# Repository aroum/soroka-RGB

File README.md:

# soroka RGB - DIY-Friendly 40% keyboard

This is a fork of the [Soroka](https://github.com/kapee1/soroka/) project with added support for the RP2040-Zero-matrix. The only modifications are to the spacer (v2), which includes a cutout to improve the viewing angle, and the addition of two optional pads on the board (v2). However, you can also use the original files with minor adjustments—see the Build Guide for more details.

### Build guide [[EN]](https://github.com/kapee1/soroka/blob/main/build%20guides/Soroka%20v2%20Build%20guide%20%5BEN%5D.md) | [[RU]](https://github.com/kapee1/soroka/blob/main/build%20guides/Soroka%20v2%20Build%20guide%20%5BRU%5D.md)

__Parts for v1 and v2 are not compatible!__

### Main features:

* Easy to build. Great for soldering practice.
* Supports all cyrillic symbols in base layer.
* Compatible with most base-kit keycap sets. No 40s addons needed.
* Optional Panasonic EVQWGD001 or EC-11 encoder
* Plate also optional. You can build keyboard without a plate to reduce cost.
* Variable bottom-row with a 3u spacebars support.
* Customizable magnet panels
* RGB matrix display 5x5
* [ZMK Studio](https://github.com/aroum/zmk-soroka)

### RGB

### Layout:

### Sizes:

## BOM:
| Part     | Quantity |
|----------|----------|
| Soroka PCB                    | 1   | 
| Soroka Plate (Optional)       | 1   | 
| Soroka Case                   | 1   | 
| Soroka Panel  (clear)         | 1   | 
| Soroka Spacer (mod)           | 1   | 
| RP2040-Zero-matrix (unsoldered pins) | 1   | 
| 1N4148w SOD-123 Diodes        | 50  | 
| Panasonic EVQWGD001 (optional)| 1   |  
| Oval feets 22x4x1.5mm         | 4   |  
| Silicone washers 2x5x1        | 9   |
| M2 x 4mm Screws               | 13  |  
| M2 Inserts 3mm (OD3.2)        | 13  |  
| Round magnets 3x1 mm          | 8   |

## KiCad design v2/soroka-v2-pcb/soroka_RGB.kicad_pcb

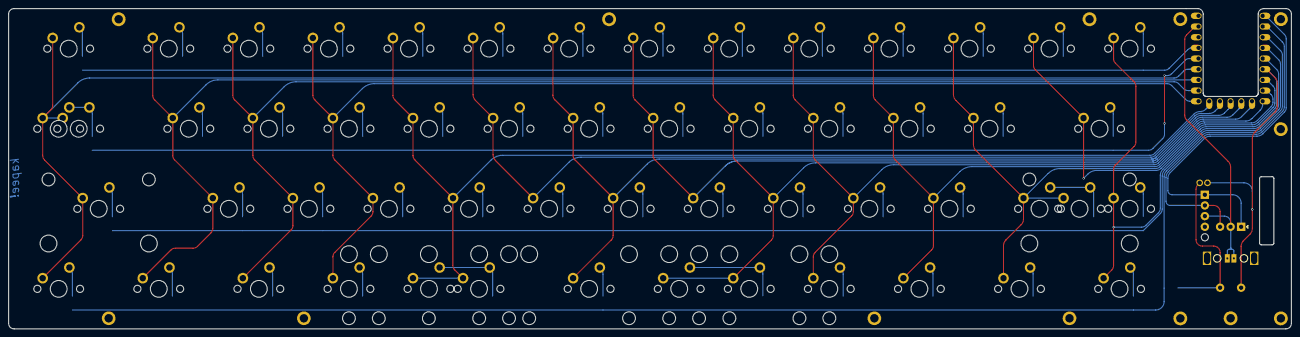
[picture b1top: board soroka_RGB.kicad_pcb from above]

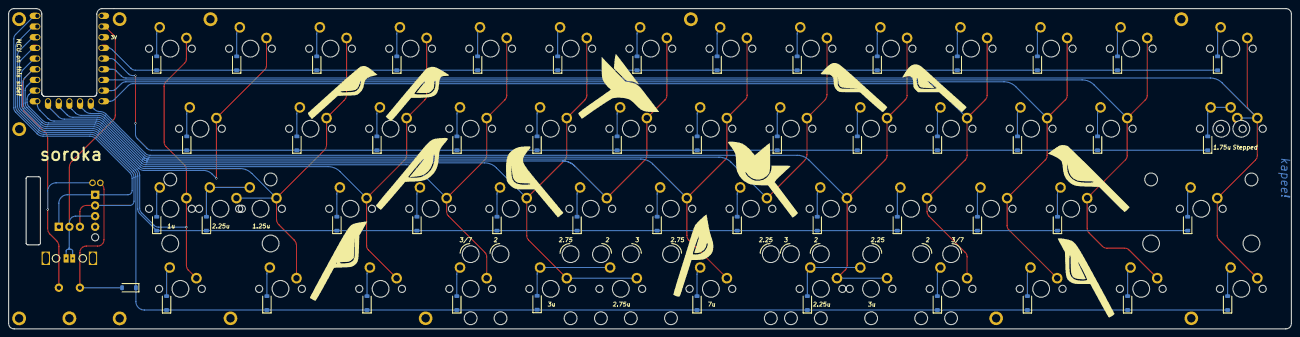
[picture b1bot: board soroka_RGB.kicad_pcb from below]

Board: 2 copper layers, 305.2 x 76.2 mm, 115 parts (52 on the bottom side), 73 nets.

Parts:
D1, D2, D3, D4, D5, D6, D7, D8, D9, D10, D11, D12, D13, D14, D15, D16, D17, D18, D19, D20, D21, D22, D23, D24, D25, D26, D27, D28, D29, D30, D31, D32, D33, D34, D35, D36, D37, D38, D39, D40, D41, D42, D43, D44, D45, D46, D47, D48, D49, D50, D51, D52: 1N4148W; D_SOD-123
MP: (no value)
RSW1, RSW1#2: SW_PUSH; SW_3x4x2_2legs_x2
SW1: MX150
SW2, SW3#2, SW4, SW5, SW6, SW7, SW8, SW9, SW10, SW11, SW12, SW13, SW14, SW16, SW17, SW18, SW19, SW20, SW21, SW22, SW23, SW24, SW25, SW26, SW29, SW30, SW31, SW32, SW33, SW34, SW35, SW36, SW37, SW38, SW45, SW50: MX100
SW3: Rotary_Encoder_Switch; EVQWGD001
SW15: Stepped; MX125
SW27: MX175
SW28: MX225R; MX225
SW39: 1.25u; MX125
SW40: 2.25u; MX225
SW41: 1u; MX100
SW42, SW43, SW44, SW51, SW52, SW53: MX125
SW46, SW49: 3u; MX300R
SW47: 2.25u; MX225R
SW48: 7u; MX100
SW54: 2.75u; MX275R
SW55: RotaryEncoder_Switch; RotaryEncoder_Alps_EC11E-Switch_Vertical_H20mm
SW55#2: 1.75u; MX175
SW**: MX200R
SW**#2: MX200R
U1: RP2040-Zero; MCU_rp2040-zero-tht

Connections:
COL0: SW1.2 (Row), SW15.2 (Row), SW28.2 (Row), SW42.2 (Row), SW55#2.2, U1.18
COL1: SW2.2 (Row), SW16.2 (Row), SW29.2 (Row), SW43.2 (Row), U1.17
COL2: SW3#2.2 (Row), SW17.2 (Row), SW30.2 (Row), SW44.2 (Row), U1.16
COL3: SW4.2 (Row), SW18.2 (Row), SW31.2 (Row), SW45.2 (Row), U1.15
COL4: SW5.2 (Row), SW19.2 (Row), SW32.2 (Row), SW46.2 (Row), SW47.2 (Row), U1.14
COL5: SW6.2 (Row), SW20.2 (Row), SW33.2 (Row), U1.13
COL6: SW7.2 (Row), SW21.2 (Row), SW34.2 (Row), SW48.2 (Row), U1.12
COL7: SW8.2 (Row), SW22.2 (Row), SW35.2 (Row), U1.11
COL8: SW9.2 (Row), SW23.2 (Row), SW36.2 (Row), SW49.2 (Row), SW54.2 (Row), U1.10
COL9: SW10.2 (Row), SW24.2 (Row), SW37.2 (Row), SW50.2 (Row), U1.9
COL10: SW11.2 (Row), SW25.2 (Row), SW38.2 (Row), SW51.2 (Row), U1.8
COL11: SW12.2 (Row), SW26.2 (Row), SW39.2 (Row), SW40.2 (Row), SW52.2 (Row), U1.7
COL12: SW3.S2, SW13.2 (Row), SW27.2 (Row), SW55.S2, U1.6
COL13: SW14.2 (Row), SW41.2 (Row), SW53.2 (Row), U1.5
ENC_CCW: SW3.A, SW55.A, U1.1
ENC_CW: SW3.B, SW55.B, U1.2
GND: RSW1.2, RSW1#2.1, SW3.C, SW55.C, U1.22
unnamed: D1.2 (A), SW1.1 (Col)
unnamed: D2.2 (A), SW2.1 (Col)
unnamed: D3.2 (A), SW3#2.1 (Col)
unnamed: D4.2 (A), SW4.1 (Col)
unnamed: D5.2 (A), SW5.1 (Col)
unnamed: D6.2 (A), SW6.1 (Col)
unnamed: D7.2 (A), SW7.1 (Col)
unnamed: D8.2 (A), SW8.1 (Col)
unnamed: D9.2 (A), SW9.1 (Col)
unnamed: D10.2 (A), SW10.1 (Col)
unnamed: D11.2 (A), SW11.1 (Col)
unnamed: D12.2 (A), SW12.1 (Col)
unnamed: D13.2 (A), SW13.1 (Col)
unnamed: D14.2 (A), SW14.1 (Col)
unnamed: D15.2 (A), SW15.1 (Col), SW55#2.1
unnamed: D16.2 (A), SW16.1 (Col)
unnamed: D17.2 (A), SW17.1 (Col)
unnamed: D18.2 (A), SW18.1 (Col)
unnamed: D19.2 (A), SW19.1 (Col)
unnamed: D20.2 (A), SW20.1 (Col)
unnamed: D21.2 (A), SW21.1 (Col)
unnamed: D22.2 (A), SW22.1 (Col)
unnamed: D23.2 (A), SW23.1 (Col)
unnamed: D24.2 (A), SW24.1 (Col)
unnamed: D25.2 (A), SW25.1 (Col)
unnamed: D26.2 (A), SW26.1 (Col)
unnamed: D27.2 (A), SW27.1 (Col)
unnamed: D28.2 (A), SW28.1 (Col)
unnamed: D29.2 (A), SW29.1 (Col)
unnamed: D30.2 (A), SW30.1 (Col)
unnamed: D31.2 (A), SW31.1 (Col)
unnamed: D32.2 (A), SW32.1 (Col)
unnamed: D33.2 (A), SW33.1 (Col)
unnamed: D34.2 (A), SW34.1 (Col)
unnamed: D35.2 (A), SW35.1 (Col)
unnamed: D36.2 (A), SW36.1 (Col)
unnamed: D37.2 (A), SW37.1 (Col)
unnamed: D38.2 (A), SW38.1 (Col)
unnamed: D39.2 (A), SW39.1 (Col), SW40.1 (Col)
unnamed: D40.2 (A), SW3.S1, SW55.S1
unnamed: D41.2 (A), SW41.1 (Col)
unnamed: D42.2 (A), SW53.1 (Col)
unnamed: D43.2 (A), SW52.1 (Col)
unnamed: D44.2 (A), SW51.1 (Col)
unnamed: D45.2 (A), SW50.1 (Col)
unnamed: D46.2 (A), SW49.1 (Col), SW54.1 (Col)
unnamed: D47.2 (A), SW48.1 (Col)
unnamed: D48.2 (A), SW46.1 (Col), SW47.1 (Col)
unnamed: D49.2 (A), SW45.1 (Col)
unnamed: D50.2 (A), SW44.1 (Col)
unnamed: D51.2 (A), SW43.1 (Col)
unnamed: D52.2 (A), SW42.1 (Col)
ROW0: D1.1 (K), D2.1 (K), D3.1 (K), D4.1 (K), D5.1 (K), D6.1 (K), D7.1 (K), D8.1 (K), D9.1 (K), D10.1 (K), D11.1 (K), D12.1 (K), D13.1 (K), D14.1 (K), U1.20
ROW1: D15.1 (K), D16.1 (K), D17.1 (K), D18.1 (K), D19.1 (K), D20.1 (K), D21.1 (K), D22.1 (K), D23.1 (K), D24.1 (K), D25.1 (K), D26.1 (K), D27.1 (K), U1.19
ROW2: D28.1 (K), D29.1 (K), D30.1 (K), D31.1 (K), D32.1 (K), D33.1 (K), D34.1 (K), D35.1 (K), D36.1 (K), D37.1 (K), D38.1 (K), D39.1 (K), D41.1 (K), U1.4
ROW3: D40.1 (K), D42.1 (K), D43.1 (K), D44.1 (K), D45.1 (K), D46.1 (K), D47.1 (K), D48.1 (K), D49.1 (K), D50.1 (K), D51.1 (K), D52.1 (K), U1.3

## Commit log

2024-11-08 init
